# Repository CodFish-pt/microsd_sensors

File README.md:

# microsd_sensors
Micro SDCard form factor for sensors

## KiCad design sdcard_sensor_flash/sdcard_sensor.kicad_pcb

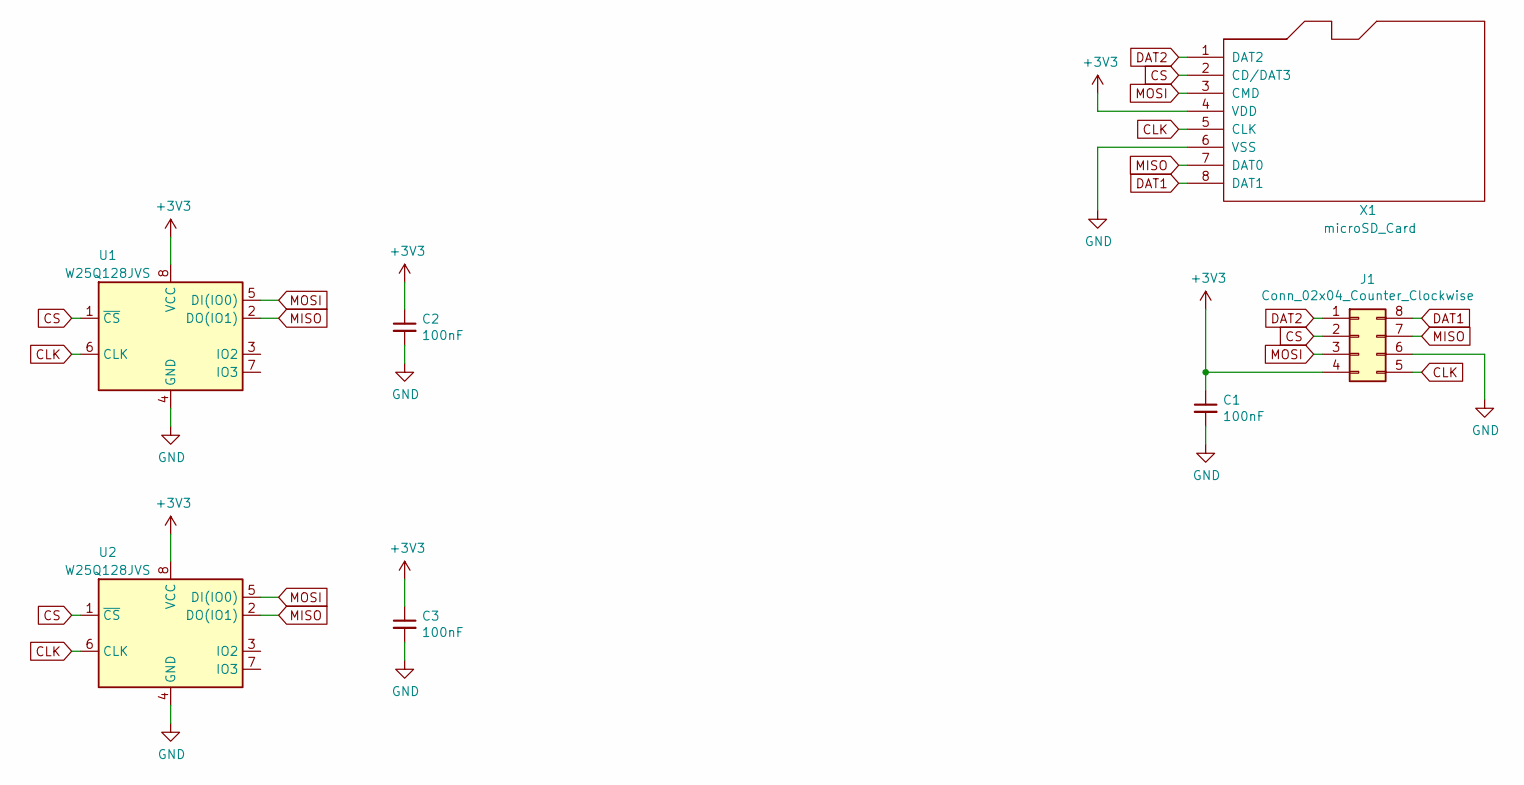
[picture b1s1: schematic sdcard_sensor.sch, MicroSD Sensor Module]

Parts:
C1, C2, C3: 100nF; C_0402_1005Metric
J1: Conn_02x04_Counter_Clockwise; PinSocket_2x04_P2.00mm_Vertical
U1: W25Q128JVS; SOIC-8_5.23x5.23mm_P1.27mm
U2: W25Q128JVS; SON40P170X150X60-9N
X1: microSD_Card

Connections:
+3V3: C1.1, C2.1, C3.1, J1.4, U1.8 (VCC), U2.8 (VCC), X1.4 (VDD)
CLK: J1.5, U1.6 (CLK), U2.6 (CLK), X1.5 (CLK)
CS: J1.2, U1.1 (~CS), U2.1 (~CS), X1.2 (CD/DAT3)
DAT1: J1.8, X1.8 (DAT1)
DAT2: J1.1, X1.1 (DAT2)
GND: C1.2, C2.2, C3.2, J1.6, U1.4 (GND), U2.4 (GND), X1.6 (VSS)
MISO: J1.7, U1.2 (DO(IO1)), U2.2 (DO(IO1)), X1.7 (DAT0)
MOSI: J1.3, U1.5 (DI(IO0)), U2.5 (DI(IO0)), X1.3 (CMD)

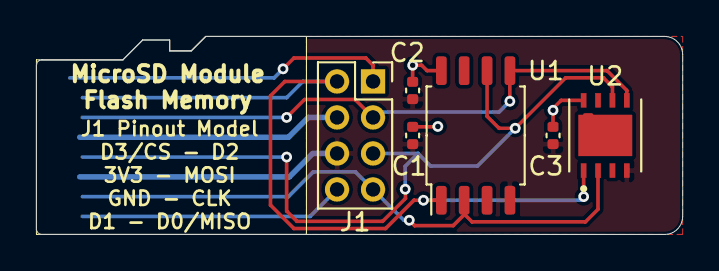
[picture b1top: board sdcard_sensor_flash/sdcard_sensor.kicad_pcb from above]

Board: 2 copper layers, 35.9 x 11.0 mm, 7 parts (0 on the bottom side), 8 nets.

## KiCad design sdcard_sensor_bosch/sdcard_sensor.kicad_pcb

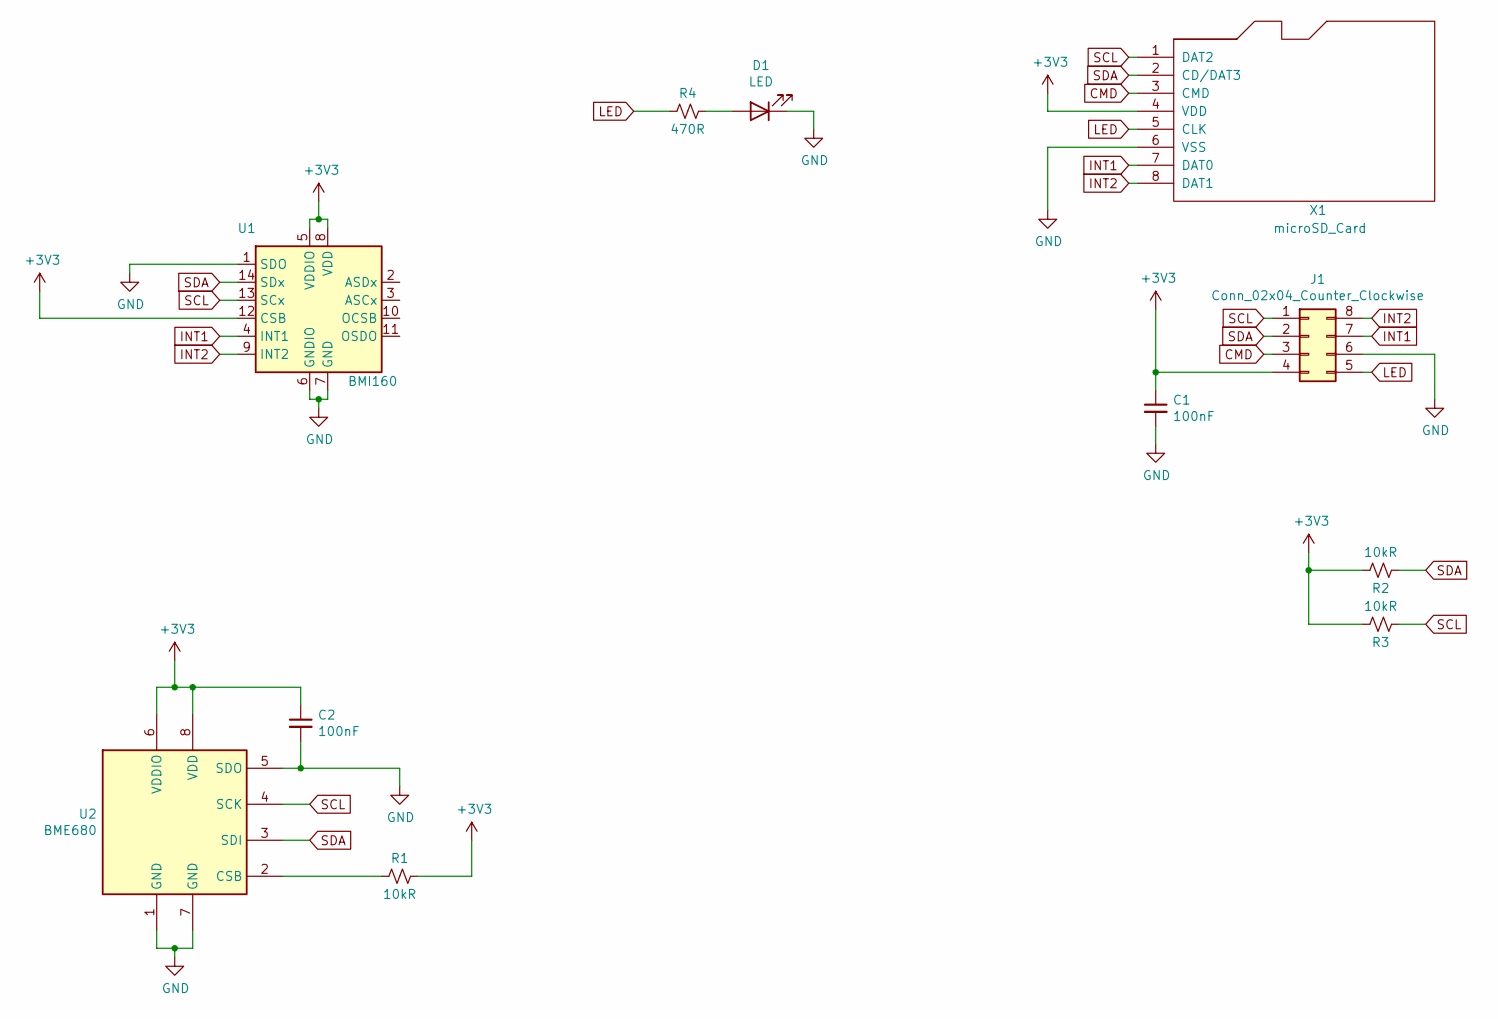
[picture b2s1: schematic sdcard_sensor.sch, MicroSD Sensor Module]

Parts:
C1, C2: 100nF; C_0402_1005Metric
D1: LED; LED_0603_1608Metric
J1: Conn_02x04_Counter_Clockwise; PinSocket_2x04_P2.00mm_Vertical
R1, R2, R3: 10kR; R_0402_1005Metric
R4: 470R; R_0402_1005Metric
U1: BMI160; Bosch_LGA-14_3x2.5mm_P0.5mm
U2: BME680; Bosch_LGA-8_3x3mm_P0.8mm_ClockwisePinNumbering
X1: microSD_Card

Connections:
+3V3: C1.1, C2.1, J1.4, R1.1, R2.1, R3.1, U1.5 (VDDIO), U1.8 (VDD), U1.12 (CSB), U2.6 (VDDIO), U2.8 (VDD), X1.4 (VDD)
CMD: J1.3, X1.3 (CMD)
GND: C1.2, C2.2, D1.1 (K), J1.6, U1.1 (SDO), U1.6 (GNDIO), U1.7 (GND), U2.1 (GND), U2.5 (SDO), U2.7 (GND), X1.6 (VSS)
INT1: J1.7, U1.4 (INT1), X1.7 (DAT0)
INT2: J1.8, U1.9 (INT2), X1.8 (DAT1)
LED: J1.5, R4.2, X1.5 (CLK)
unnamed: D1.2 (A), R4.1
unnamed: R1.2, U2.2 (CSB)
SCL: J1.1, R3.2, U1.13 (SCx), U2.4 (SCK), X1.1 (DAT2)
SDA: J1.2, R2.2, U1.14 (SDx), U2.3 (SDI), X1.2 (CD/DAT3)

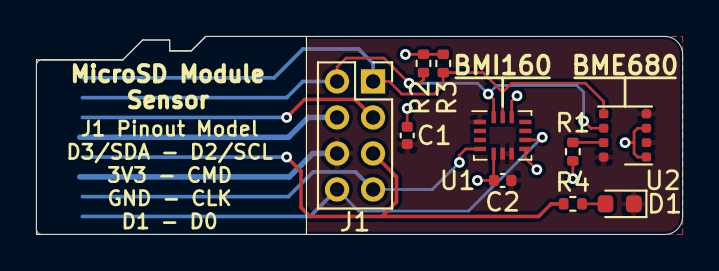
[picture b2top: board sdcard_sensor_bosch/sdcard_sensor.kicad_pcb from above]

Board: 2 copper layers, 35.9 x 11.0 mm, 11 parts (0 on the bottom side), 10 nets.

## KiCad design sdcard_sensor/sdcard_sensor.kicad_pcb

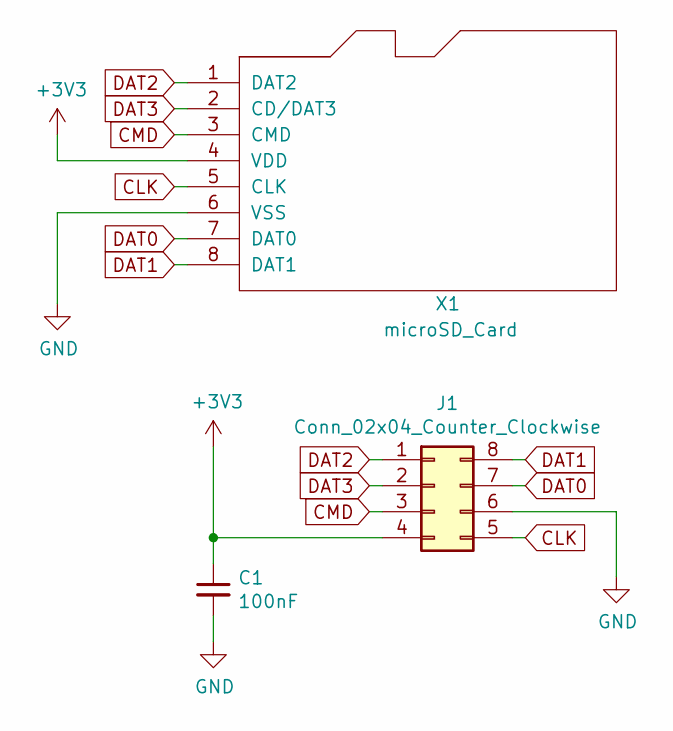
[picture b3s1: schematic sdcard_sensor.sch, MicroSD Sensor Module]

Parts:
C1: 100nF; C_0402_1005Metric
J1: Conn_02x04_Counter_Clockwise; PinSocket_2x04_P2.00mm_Vertical
X1: microSD_Card

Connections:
+3V3: C1.1, J1.4, X1.4 (VDD)
CLK: J1.5, X1.5 (CLK)
CMD: J1.3, X1.3 (CMD)
DAT0: J1.7, X1.7 (DAT0)
DAT1: J1.8, X1.8 (DAT1)
DAT2: J1.1, X1.1 (DAT2)
DAT3: J1.2, X1.2 (CD/DAT3)
GND: C1.2, J1.6, X1.6 (VSS)

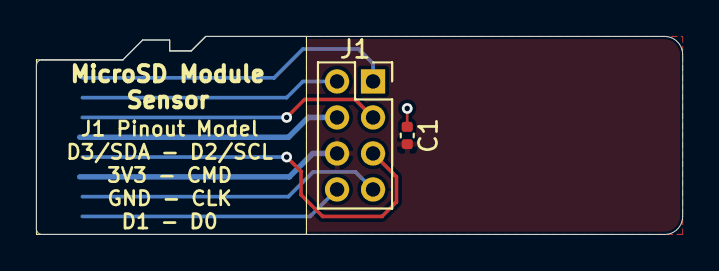
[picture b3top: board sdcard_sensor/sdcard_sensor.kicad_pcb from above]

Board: 2 copper layers, 35.9 x 11.0 mm, 3 parts (0 on the bottom side), 8 nets.

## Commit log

2021-02-14 Added project base
2021-02-21 Format changed
2021-02-21 Template done
2021-02-21 Added Bosch sensors module
2021-02-21 Silk fixed
2021-02-21 Added flash memory module
